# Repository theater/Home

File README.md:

Home
====
Arduino section contains my scetches for temperature control of aquarium + MQTT settings in two sketches - one for SSR relays regular logic, and one for chinese relay boards where negative logic is used (low level triggers relay).

Beaglebone section contains device overlays for beaglebone that I use and some scripts

OpenHAB section contains my openhab configurations

My Home automation projects

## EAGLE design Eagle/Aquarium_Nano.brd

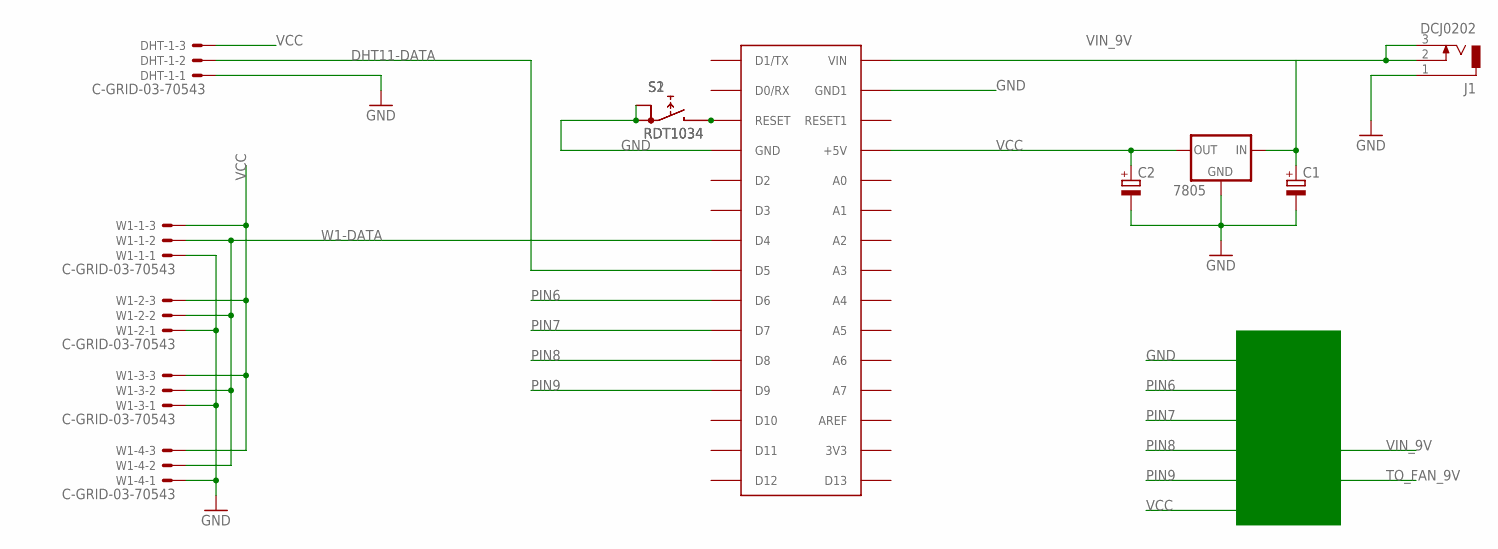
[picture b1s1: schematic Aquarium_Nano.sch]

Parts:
7805: V_REG_78XX-TO-220; TO-220-ALT
C1, C2: CPOL-EUE2.5-6; E2,5-6
DHT-1: C-GRID-03-70543; 70543-03
J1: DCJ0202
S1, S2: RDT1034
U$2: ARDUINONANO; PDIP-32
W1-1, W1-2, W1-3, W1-4: C-GRID-03-70543; 70543-03

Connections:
DHT11-DATA: DHT-1.2, U$2.D5
GND: 7805.GND, C1.-, C2.-, DHT-1.1, J1.1, S1.A, S1.A1, S2.A, S2.A1, U$2.GND, U$2.GND1, W1-1.1, W1-2.1, W1-3.1, W1-4.1
unnamed: S1.B, S2.B, U$2.RESET
PIN6: U$2.D6
PIN7: U$2.D7
PIN8: U$2.D8
PIN9: U$2.D9
VCC: 7805.OUT, C2.+, DHT-1.3, U$2.+5V, W1-1.3, W1-2.3, W1-3.3, W1-4.3
VIN_9V: 7805.IN, C1.+, J1.2, J1.3, U$2.VIN
W1-DATA: U$2.D4, W1-1.2, W1-2.2, W1-3.2, W1-4.2

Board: 2 copper layers, 12 parts (0 on the bottom side), 6 nets, no tracks yet.

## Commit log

2014-08-02 new origin commit
2014-08-03 Final changes eventually. :)
2014-08-06 manual logic if MQTT down added
2014-08-06 small change
2014-08-11 11Aug2014
2014-09-03 Final version SSR relays
2014-09-04 Tests only
2014-09-04 Final SSR, some logic for data quality added
2014-09-26 nRF24L01+ examples
2014-09-26 nRF24L01+ library
2014-09-26 minor changes in Configurations
2014-09-26 Readme
2014-09-28 Improved sitemap
2014-10-18 New commit
2014-10-27 Updates for Ethernet restart issue
2014-11-19 Weatherstation_v1
2014-11-19 Added WeatherUnderground transformations
2014-11-24 Floating point issues fix
2014-11-25 DS2413 first attempt
2015-01-07 Minor rules changes, workaround for persistence restore
2015-01-26 First ESP8266 commit
2015-01-28 LR Heater v.1.0
2015-01-30 LR Heater.0.1
2015-01-31 test
2015-01-31 Got rid of CFG_SAVE
2015-02-08 Bathroom sources
2015-02-11 Almost done...
2015-02-11 Bathroom ESP8266 done
2015-02-15 Added support for reading GPIO12 as contact
2015-02-16 Latest BATHROOM with input pin read
2015-02-17 Some OpenHAB changes
2015-02-19 Updates in OpenHAB
2015-02-19 Some pics of ESP8266
2015-03-08 Aquarium V2
2015-07-12 Bathroom Soft button
2015-10-23 New OpenHab configurations
2017-02-21 Initial implementation of Bathroom mirror heating control
2017-02-21 Removed unnecessary files
2017-02-21 Should be fine. To be tested with hardware.
    Initial logic is done using interrupt for the trigger and timer for off.
2017-02-22 Almost stable without DHT stuff. Tried it with hardware

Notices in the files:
parts and their libraries:
SparkFun-PowerIC: Licensing: CC v3.0 Share-Alike You are welcome to use this library for commercial purposes.
